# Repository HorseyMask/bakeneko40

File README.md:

# bakeneko40

## On Hold / WIP. Nothing here works (probably), please don't actually try to make this

### Do have interest in working on this again, but still consider this on hold until further work is done.

40% verison of the bakenkeo40 keyboard by kkatano. 

PCB is still in testing and unconfirmed to work, but otherwise project is mostly done.

Case is a bit too big for plate and pcb. Either edit case or use foam between pcb and plate to allow more room for oring.

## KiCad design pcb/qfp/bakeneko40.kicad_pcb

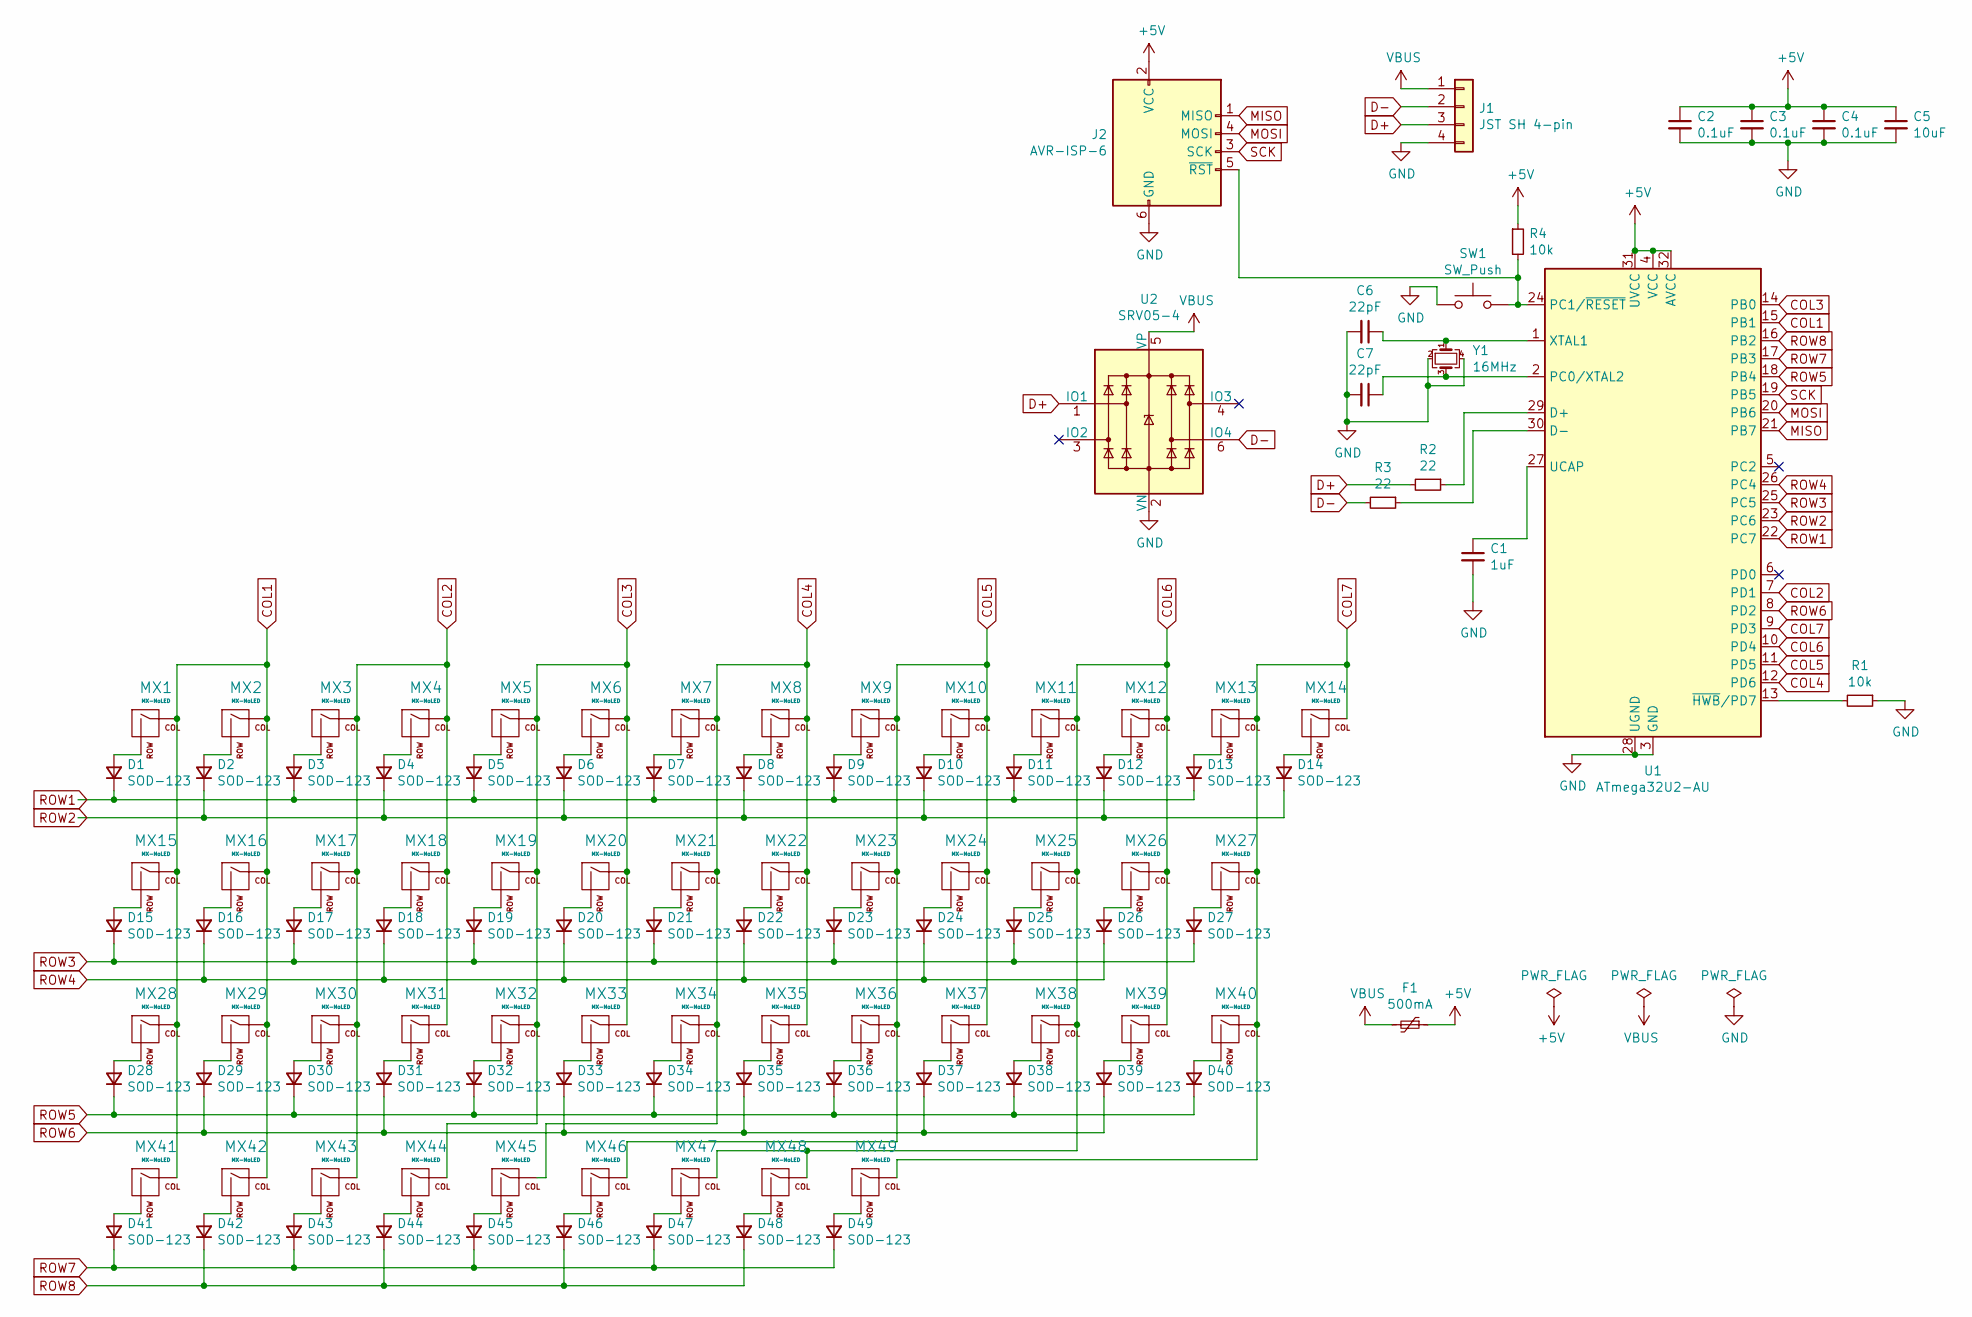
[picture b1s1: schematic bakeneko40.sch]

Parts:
C1: 1uF; C_0805_2012Metric
C2, C3, C4: 0.1uF; C_0805_2012Metric
C5: 10uF; C_0805_2012Metric
C6, C7: 22pF; C_0805_2012Metric
D1, D2, D3, D4, D5, D6, D7, D8, D9, D10, D11, D12, D13, D14, D15, D16, D17, D18, D19, D20, D21, D22, D23, D24, D25, D26, D27, D28, D29, D30, D31, D32, D33, D34, D35, D36, D37, D38, D39, D40, D41, D42, D43, D44, D45, D46, D47, D48, D49: SOD-123; D_SOD-123
F1: 500mA; Fuse_1206_3216Metric
J1: JST SH 4-pin; JST-SR-4
J2: AVR-ISP-6; Reset_Pretty-Mask
MX1, MX2, MX3, MX4, MX5, MX6, MX7, MX8, MX9, MX10, MX11, MX12, MX13, MX14, MX16, MX17, MX18, MX19, MX20, MX21, MX22, MX23, MX24, MX25, MX26, MX29, MX30, MX31, MX32, MX33, MX34, MX35, MX36, MX37, MX38, MX40, MX49: MX-NoLED; MXOnly-1U-NoLED
MX15, MX39, MX41, MX43, MX46, MX48: MX-NoLED; MXOnly-1.25U-NoLED
MX27, MX28: MX-NoLED; MXOnly-1.75U-NoLED
MX42, MX47: MX-NoLED; MXOnly-1.5U-NoLED
MX44: MX-NoLED; MXOnly-2.25U-ReversedStabilizers-NoLED
MX45: MX-NoLED; MXOnly-2.75U-ReversedStabilizers-NoLED
R1, R4: 10k; R_0805_2012Metric
R2, R3: 22; R_0805_2012Metric
SW1: SW_Push; SKQG-1155865
U1: ATmega32U2-AU; TQFP-32_7x7mm_P0.8mm
U2: SRV05-4; SOT-23-6
Y1: 16MHz; Crystal_SMD_3225-4Pin_3.2x2.5mm

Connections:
+5V: C2.1, C3.1, C4.1, C5.1, F1.1, J2.2 (VCC), R4.1, U1.4 (VCC), U1.31 (UVCC), U1.32 (AVCC)
COL1: MX1.1 (COL), MX2.1 (COL), MX15.1 (COL), MX16.1 (COL), MX28.1 (COL), MX29.1 (COL), MX41.1 (COL), MX42.1 (COL), U1.15 (PB1)
COL2: MX3.1 (COL), MX4.1 (COL), MX17.1 (COL), MX18.1 (COL), MX30.1 (COL), MX31.1 (COL), MX43.1 (COL), U1.7 (PD1)
COL3: MX5.1 (COL), MX6.1 (COL), MX19.1 (COL), MX20.1 (COL), MX32.1 (COL), MX33.1 (COL), MX44.1 (COL), U1.14 (PB0)
COL4: MX7.1 (COL), MX8.1 (COL), MX21.1 (COL), MX22.1 (COL), MX34.1 (COL), MX35.1 (COL), MX45.1 (COL), U1.12 (PD6)
COL5: MX9.1 (COL), MX10.1 (COL), MX23.1 (COL), MX24.1 (COL), MX36.1 (COL), MX37.1 (COL), MX46.1 (COL), U1.11 (PD5)
COL6: MX11.1 (COL), MX12.1 (COL), MX25.1 (COL), MX26.1 (COL), MX38.1 (COL), MX39.1 (COL), MX47.1 (COL), MX48.1 (COL), U1.10 (PD4)
COL7: MX13.1 (COL), MX14.1 (COL), MX27.1 (COL), MX40.1 (COL), MX49.1 (COL), U1.9 (PD3)
D+: J1.3, R2.2, U2.1 (IO1)
D-: J1.2, R3.2, U2.6 (IO4)
GND: C1.2, C2.2, C3.2, C4.2, C5.2, C6.2, C7.2, J1.4, J2.6 (GND), R1.1, SW1.1, U1.3 (GND), U1.28 (UGND), U2.2 (VN), Y1.2, Y1.4
MISO: J2.1 (MISO), U1.21 (PB7)
MOSI: J2.4 (MOSI), U1.20 (PB6)
unnamed: C1.1, U1.27 (UCAP)
unnamed: C6.1, U1.1 (XTAL1), Y1.1
unnamed: C7.1, U1.2 (PC0/XTAL2), Y1.3
unnamed: D1.2 (A), MX1.2 (ROW)
unnamed: D2.2 (A), MX2.2 (ROW)
unnamed: D3.2 (A), MX3.2 (ROW)
unnamed: D4.2 (A), MX4.2 (ROW)
unnamed: D5.2 (A), MX5.2 (ROW)
unnamed: D6.2 (A), MX6.2 (ROW)
unnamed: D7.2 (A), MX7.2 (ROW)
unnamed: D8.2 (A), MX8.2 (ROW)
unnamed: D9.2 (A), MX9.2 (ROW)
unnamed: D10.2 (A), MX10.2 (ROW)
unnamed: D11.2 (A), MX11.2 (ROW)
unnamed: D12.2 (A), MX12.2 (ROW)
unnamed: D13.2 (A), MX13.2 (ROW)
unnamed: D14.2 (A), MX14.2 (ROW)
unnamed: D15.2 (A), MX15.2 (ROW)
unnamed: D16.2 (A), MX16.2 (ROW)
unnamed: D17.2 (A), MX17.2 (ROW)
unnamed: D18.2 (A), MX18.2 (ROW)
unnamed: D19.2 (A), MX19.2 (ROW)
unnamed: D20.2 (A), MX20.2 (ROW)
unnamed: D21.2 (A), MX21.2 (ROW)
unnamed: D22.2 (A), MX22.2 (ROW)
unnamed: D23.2 (A), MX23.2 (ROW)
unnamed: D24.2 (A), MX24.2 (ROW)
unnamed: D25.2 (A), MX25.2 (ROW)
unnamed: D26.2 (A), MX26.2 (ROW)
unnamed: D27.2 (A), MX27.2 (ROW)
unnamed: D28.2 (A), MX28.2 (ROW)
unnamed: D29.2 (A), MX29.2 (ROW)
unnamed: D30.2 (A), MX30.2 (ROW)
unnamed: D31.2 (A), MX31.2 (ROW)
unnamed: D32.2 (A), MX32.2 (ROW)
unnamed: D33.2 (A), MX33.2 (ROW)
unnamed: D34.2 (A), MX34.2 (ROW)
unnamed: D35.2 (A), MX35.2 (ROW)
unnamed: D36.2 (A), MX36.2 (ROW)
unnamed: D37.2 (A), MX37.2 (ROW)
unnamed: D38.2 (A), MX38.2 (ROW)
unnamed: D39.2 (A), MX39.2 (ROW)
unnamed: D40.2 (A), MX40.2 (ROW)
unnamed: D41.2 (A), MX41.2 (ROW)
unnamed: D42.2 (A), MX42.2 (ROW)
unnamed: D43.2 (A), MX43.2 (ROW)
unnamed: D44.2 (A), MX44.2 (ROW)
unnamed: D45.2 (A), MX45.2 (ROW)
unnamed: D46.2 (A), MX46.2 (ROW)
unnamed: D47.2 (A), MX47.2 (ROW)
unnamed: D48.2 (A), MX48.2 (ROW)
unnamed: D49.2 (A), MX49.2 (ROW)
unnamed: J2.5 (~RST), R4.2, SW1.2, U1.24 (PC1/~RESET)
unnamed: R1.2, U1.13 (~HWB~/PD7)
unnamed: R2.1, U1.29 (D+)
unnamed: R3.1, U1.30 (D-)
ROW1: D1.1 (K), D3.1 (K), D5.1 (K), D7.1 (K), D9.1 (K), D11.1 (K), D13.1 (K), U1.22 (PC7)
ROW2: D2.1 (K), D4.1 (K), D6.1 (K), D8.1 (K), D10.1 (K), D12.1 (K), D14.1 (K), U1.23 (PC6)
ROW3: D15.1 (K), D17.1 (K), D19.1 (K), D21.1 (K), D23.1 (K), D25.1 (K), D27.1 (K), U1.25 (PC5)
ROW4: D16.1 (K), D18.1 (K), D20.1 (K), D22.1 (K), D24.1 (K), D26.1 (K), U1.26 (PC4)
ROW5: D28.1 (K), D30.1 (K), D32.1 (K), D34.1 (K), D36.1 (K), D38.1 (K), D40.1 (K), U1.18 (PB4)
ROW6: D29.1 (K), D31.1 (K), D33.1 (K), D35.1 (K), D37.1 (K), D39.1 (K), U1.8 (PD2)
ROW7: D41.1 (K), D43.1 (K), D45.1 (K), D47.1 (K), D49.1 (K), U1.17 (PB3)
ROW8: D42.1 (K), D44.1 (K), D46.1 (K), D48.1 (K), U1.16 (PB2)
SCK: J2.3 (SCK), U1.19 (PB5)
VBUS: F1.2, J1.1, U2.5 (VP)

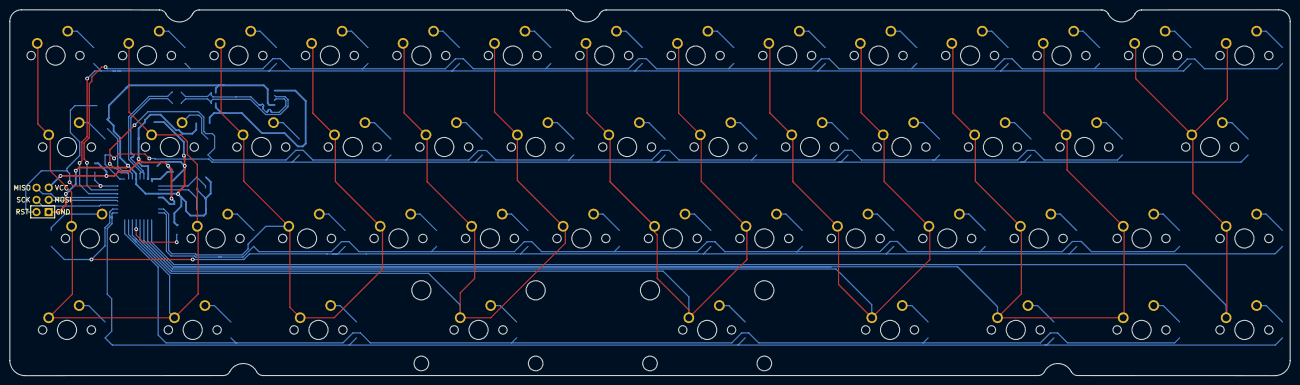
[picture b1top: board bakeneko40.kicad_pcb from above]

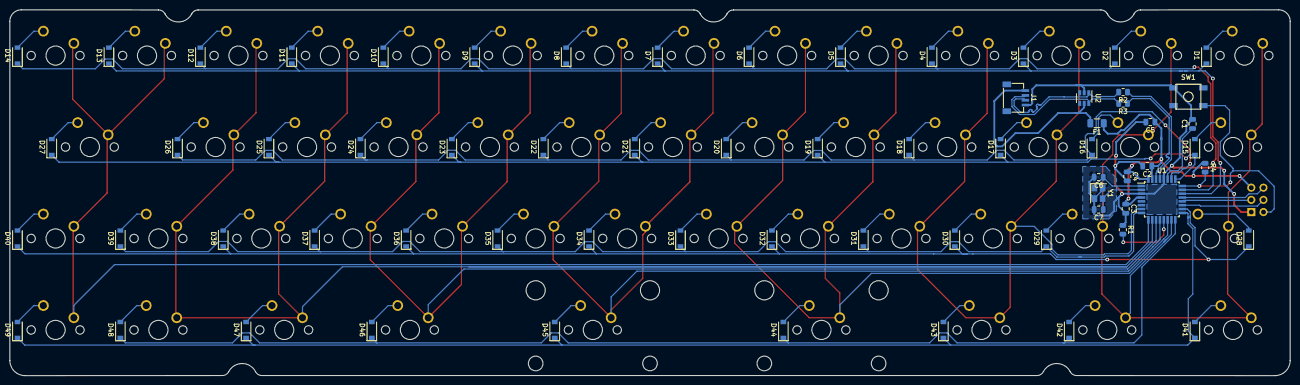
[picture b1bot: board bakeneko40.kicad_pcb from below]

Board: 2 copper layers, 266.7 x 76.2 mm, 116 parts (66 on the bottom side), 79 nets.

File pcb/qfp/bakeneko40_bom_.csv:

Component,Description,Part,References,Value,Footprint,Quantity Per PCB,Datasheet
1,"Unpolarized capacitor, small symbol",C_Small,C6 C7,22pF,C_0805_2012Metric,2,~
2,"Unpolarized capacitor, small symbol",C_Small,C2 C3 C4,0.1uF,C_0805_2012Metric,3,~
3,"Unpolarized capacitor, small symbol",C_Small,C1,1uF,C_0805_2012Metric,1,~
4,"Unpolarized capacitor, small symbol",C_Small,C5,10uF,C_0805_2012Metric,1,~
5,"Diode, small symbol",D_Small,D1 D2 D3 D4 D5 D6 D7 D8 D9 D10 D11 D12 D13 D14 D15 D16 D17 D18 D19 D20 D21 D22 D23 D24 D25 D26 D27 D28 D29 D30 D31 D32 D33 D34 D35 D36 D37 D38 D39 D40 D41 D42 D43 D44 D45 D46 D47 D48 D49,SOD-123,D_SOD-123,49,~
6,"Resettable fuse, polymeric positive temperature coefficient, small symbol",Polyfuse_Small,F1,500mA,Fuse_1206_3216Metric,1,~
7,Atmel 6-pin ISP connector,AVR-ISP-6,J2,AVR-ISP-6,Reset_Pretty-Mask,1, ~
8,"Generic connector, single row, 01x04, script generated (kicad-library-utils/schlib/autogen/connector/)",Conn_01x04,J1,JST SH 4-pin,JST-SR-4,1,~
9,,MX-NoLED,MX1 MX2 MX3 MX4 MX5 MX6 MX7 MX8 MX9 MX10 MX11 MX12 MX13 MX14 MX16 MX17 MX18 MX19 MX20 MX21 MX22 MX23 MX24 MX25 MX26 MX29 MX30 MX31 MX32 MX33 MX34 MX35 MX36 MX37 MX38 MX40 MX49,MX-NoLED,MXOnly-1U-NoLED,37,
10,,MX-NoLED,MX15 MX39 MX41 MX43 MX46 MX48,MX-NoLED,MXOnly-1.25U-NoLED,6,
11,,MX-NoLED,MX27 MX28,MX-NoLED,MXOnly-1.75U-NoLED,2,
12,,MX-NoLED,MX42 MX47,MX-NoLED,MXOnly-1.5U-NoLED,2,
13,,MX-NoLED,MX44,MX-NoLED,MXOnly-2.25U-ReversedStabilizers-NoLED,1,
14,,MX-NoLED,MX45,MX-NoLED,MXOnly-2.75U-ReversedStabilizers-NoLED,1,
15,"Resistor, small symbol",R_Small,R2 R3,22,R_0805_2012Metric,2,~
16,"Resistor, small symbol",R_Small,R1 R4,10k,R_0805_2012Metric,2,~
17,"Push button switch, generic, two pins",SW_Push,SW1,SW_Push,SKQG-1155865,1,~
18,"16MHz, 32kB Flash, 1kB SRAM, 1kB EEPROM, TQFP-32",ATmega32U2-AU,U1,ATmega32U2-AU,TQFP-32_7x7mm_P0.8mm,1,http://ww1.microchip.com/downloads/en/DeviceDoc/doc7799.pdf
19,"ESD Protection Diodes with Low Clamping Voltage, SOT-23-6",SRV05-4,U2,SRV05-4,SOT-23-6,1,http://www.onsemi.com/pub/Collateral/SRV05-4-D.PDF
20,"Four pin crystal, GND on pins 2 and 4, small symbol",Crystal_GND24_Small,Y1,16MHz,Crystal_SMD_3225-4Pin_3.2x2.5mm,1,~





Component Groups:,20
Component Count:,116
Fitted Components:,116
Number of PCBs:,1
Total components:,116
Schematic Version:,
Schematic Date:,
PCB Variant:,default
BoM Date:,Fri 09 Jul 2021 03:37:36 PM KST
Schematic Source:,bakeneko40.sch
KiCad Version:,Eeschema 5.1.10

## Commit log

2021-06-13 initial
2021-06-13 add submodules
2021-06-13 layout+pcb work
2021-06-13 full alpha case add
2021-06-13 sch updates
2021-06-15 pcb routing
2021-06-16 finished pcb
2021-06-16 pcb cut edits
2021-06-18 final pcb and case
2021-06-19 qmk code
2021-06-19 2d drawing
2021-07-01 qfp pcb
2021-07-09 pcb and qmk edits
2021-07-21 final edits
2023-03-22 Update README.md
    maybe i'll work on this again
